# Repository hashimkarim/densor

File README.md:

# Densor

## About the project

Densor is an intraoral sensor platform, attached to regular dental retainers or aligners, that can take measurements inside the mouth. 

## Rationale

At present, in mouth measurements are typically made with external tools and in a controlled labaratory setting. Thus, real data from users daily lives is missing. To overcome this, we propose using widely used deltal retainers (or aligners), and enhance them with the Densor sensing platform. This way data is collected from inside the mouth without external tools. 

## Features

1. **Contactless transmission:** Densor is completely sealed and interacts with a smartphone via [NFC protocol](https://en.wikipedia.org/wiki/Near-field_communication). 
2. **Energy harvesting:** To stay powered Densor harvests energy, either from the [NFC communication itself](https://github.com/TUDSSL/densor/tree/master/NFC_harvester_battery_free) or from the [temperature gradient between the body and cold water](https://github.com/TUDSSL/densor/tree/master/TEG_harvester_battery_free). 
4. **Free of external hardware:** Operating Densor does not require any specialized tools, other than a NFC-compatible smartphone.

## Project layout

For the current NFC firmware (R2/R3 multirate logging), Android app, build
commands and protocol documentation, see the [software guide](NFC_harvester_battery_free/software/README.md).

This repository contains the design (both hardware and software) of two versions of Densor, based on the source of energy harvesting. Each version of the project is contained in its own folder:

1. **[Densor with NFC-based energy harvesting from a smartphone](https://github.com/TUDSSL/densor/tree/master/NFC_harvester_battery_free)**, as presented in [this research article](https://dl.acm.org/doi/10.1145/3699746);
2. **[Densor with thermoelectric energy harvesting from drinking cold water](https://github.com/TUDSSL/densor/tree/master/TEG_harvester_battery_free)**.

## Copyright

Copyright (C) 2024 TU Delft Embedded Systems Group/[Sustainable Systems Laboratory](https://github.com/TUDSSL).

MIT License or otherwise specified. See [license](https://github.com/TUDSSL/densor/blob/master/LICENSE.txt) file for details.

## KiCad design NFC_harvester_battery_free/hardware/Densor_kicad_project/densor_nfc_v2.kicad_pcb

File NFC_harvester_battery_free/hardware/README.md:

# Densor - Hardware

The TMP119 and its 100 nF capacitor sit **14.5 mm beyond the original PCB edge**.
R2/R3 remain **100 kΩ**, C14 connects `V_MCU` to `PSW`, and ALERT is unconnected.
The neck enforces 0.15 mm tracks for `V_MCU`/SDA/SCL and 0.20 mm for `PSW`,
with no vias/components; the continuous back GND fill and repaired GND connection remain.

[Current schematic](gerbers_schematic/schematic_nfc_baterry_free_fpc.pdf) ·
[Gerbers and drills](gerbers_schematic/gerbers_fpc) ·
[PCB layout](exports/pcb.pdf) · [3D render](exports/3d-oblique.png) ·
[BOM](exports/bom.csv) · [Placements](exports/placement.csv)

The original CAD stackup is retained, including its recorded **1.6 mm** thickness.
`exports/densor_nfc_v2.step` contains the native stackup and components;
`exports/board-1.6mm.step` is the nominal board envelope. Actual flex construction
and bend radius are unspecified in the original. Model sources and licenses are in
`Densor_kicad_project/vendor/`.

Latest checks: zero unrouted connections and no new DRC/ERC/parity findings.
The 31 DRC, 19 ERC and 20 metadata findings are inherited. Final I²C, wake/sleep
and bent/epoxied fit measurements across 2.6–1.8 V remain pending.
The purchasing links below are historical; use the schematic BOM for current
values, and complete its missing MPN fields before ordering.

## About the project 

This repository contains the design of Densor: an intraoral, actively powered, battery-free platform featuring multi-modal sensors and an extended lifespan. The repository consists of all components that make Densor:
- [Hardware](https://github.com/TUDSSL/densor/tree/master/NFC_harvester_battery_free/hardware)
- [Densor Firmware](https://github.com/TUDSSL/densor/tree/master/NFC_harvester_battery_free/software/DentalSensor_StorageProject)
- [Android app](https://github.com/TUDSSL/densor/tree/master/NFC_harvester_battery_free/software/source_ST25NFCApplication_V3_9)
- [Experiment setup and data collected](https://github.com/TUDSSL/densor/tree/master/NFC_harvester_battery_free/data/experiments)

This folder contains all the harware design files.

## Folder layout

- [KiCad project](Densor_kicad_project/densor_nfc_v2.kicad_pro): current design, local symbols, footprints and all 25 component STEP models.
- [Datasheets](datasheets): component reference PDFs.
- [Gerbers and schematic](gerbers_schematic): current extension Gerbers, drills, job file and schematic PDF.
- [Exports](exports): PCB views, renders, assembly drawings, BOM, placements and STEP files.

## Historical baseline purchasing references

| Component                  | Qty | Purchased from                                                                                                                                                                                                            |
|----------------------------|-----|---------------------------------------------------------------------------------------------------------------------------------------------------------------------------------------------------------------------------|
| Storage Capacitor          | 2   | [link to buy](https://www.digikey.com/en/products/detail/seiko-instruments/CPH3225A/8692444)                                                                                                                              |
| Decoupling Capacitor 100nF | 6   | [link to buy](https://nl.farnell.com/en-NL/kemet/c0603x104m4ractu/cap-mlcc-0-1uf-16v-0603/dp/2904941?st=0603%200.1uf)                                                                                                     |
| Zener Diode                | 1   | [link to buy](https://nl.farnell.com/on-semiconductor/mm3z3v6c/zener-diode-0-2w-3-6v-sod-323f/dp/2824925?CMP=i-ddd7-00001003)                                                                                             |
| Schottky Diode             | 1   | [link to buy](https://nl.farnell.com/nexperia/1ps76sb40-115/diode-schottky-sod323/dp/1349646?CMP=i-ddd7-00001003)                                                                                                         |
| Photo Diode                | 1   | [link to buy](https://nl.mouser.com/ProductDetail/Vishay-Semiconductors/VEMD1060X01?qs=pdQl6rENvLQkGyXPnNHd%2FQ%3D%3D&gclid=Cj0KCQjwmvSoBhDOARIsAK6aV7gSam9QYNxRe1G3dFcvfZGu4WvhXWOQdtZbTP3WNCzxGxyePn8TLa0aAiUbEALw_wcB) |
| Debug header               | 1   | [link to buy](https://nl.farnell.com/samtec/ftsh-105-01-l-d-k/connector-header-10pos-2row-1/dp/2856435?CMP=i-ddd7-00001003)                                                                                               |
| FPC connector              | 1   | [link to buy](https://nl.mouser.com/ProductDetail/Molex/503480-0800?qs=bodV9ulq6Gz33SKuZL445g%3D%3D&srsltid=AfmBOoqTYanmI1YXInVOzdpLIJ4tpVXYK3TQdvr3HJ4Y6jSj3ONDx022)                                                     |
| Pin Header 01x04           | 1   | [link to buy](https://nl.mouser.com/ProductDetail/Harwin/M20-9770446?qs=ulE8k0yEMYbCPpMPHeYh4w%3D%3D)                                                                                                                     |
| Resistor 100kohm           | 3   | [link to buy](https://nl.farnell.com/vishay/crcw0603100kfkea/res-100k-1-0-1w-0603-thick-film/dp/1469649?st=0603%20100k)                                                                                                   |
| Resistor 8Mohm             | 1   | [link to buy](https://nl.farnell.com/vishay/crcw06038m06fkea/res-8m06-1-0-1w-0603-thick-film/dp/2138717)                                                                                                                  |
| NFC Tag - ST25DV04K-JFR6D3 | 1   | [link to buy](https://www.digikey.nl/en/products/detail/stmicroelectronics/ST25DV64K-JFR6D3/7312974)                                                                                                                      |
| RTC - AM1805               | 1   | [link to buy](https://nl.farnell.com/en-NL/abracon/ab1805-t3/real-time-clock-i2c-qfn-16/dp/2467703?st=ab1805)                                                                                                             |
| MCU - STM32L021F3Ux        | 1   | [link to buy](https://www.digikey.nl/en/products/detail/stmicroelectronics/STM32L021F4U6TR/6166967)                                                                                                                       |
| Accelerometer - LIS2DW12   | 1   | [link to buy](https://nl.farnell.com/en-NL/stmicroelectronics/lis2dw12tr/lga-12-i-mems-digital-o-p-motion/dp/2849615?st=LIS2DW12TR)                                                                                       |
| SPDT - TS3A44159           | 1   | [link to buy](https://www.digikey.nl/en/products/detail/texas-instruments/TS3A44159RSVR/1909585)                                                                                                                          |
| Crystal                    | 1   | [link to buy](https://nl.farnell.com/en-NL/abracon/abs05w-32-768khz-j-2-t/crystal-32-768khz-4pf-smd-1-6/dp/2850126?st=abs05w)                                                                                             |
| Solder paste               | -   | [link to buy](https://www.digikey.nl/en/products/detail/chip-quik-inc/SMD291SNL50T3/5130160)                                                                                                                              |

## Copyright

Copyright (C) 2024 TU Delft Embedded Systems Group/Sustainable Systems Laboratory.

MIT Licence or otherwise specified. See [license](https://github.com/TUDSSL/ENGAGE/blob/master/LICENSE) file for details.

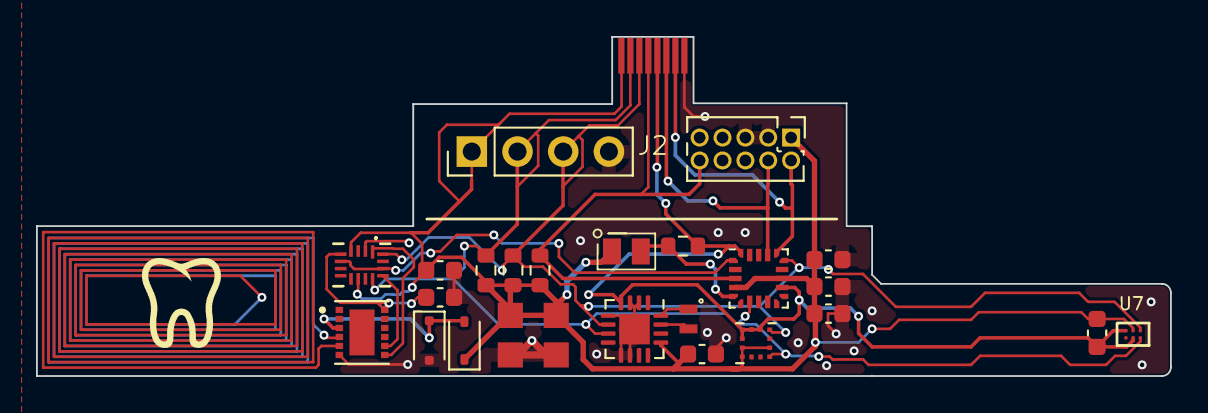
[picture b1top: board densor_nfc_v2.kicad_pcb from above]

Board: 2 copper layers, 63.0 x 18.8 mm, 26 parts (0 on the bottom side), 17 nets.

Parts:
C1, C2: C_Polarized; CPX3225A
C4, C5, C6, C7, C12, C13, C14: 100n; C_0603_1608Metric
D1: D_Zener_3v3; D_SOD-323F
D2: BAS316; D_SOD-323
D3: D_Photo; pd_vemd1060x01
J1: Conn_ARM_JTAG_SWD_10; PinHeader_2x05_P1.27mm_Vertical
J2: Conn_01x08_Pin; fpc_503480-0800
J3: Conn_01x04_Pin; PinHeader_1x04_P2.54mm_Vertical
R2, R3, R4: 100k; R_0603_1608Metric
R7: R; R_0603_1608Metric
U1: ST25DV04K-JFR6D3; PSON50P300X300X60-13N
U2: AM1805; QFN-16-1EP_3x3mm_P0.5mm_EP1.7x1.7mm
U4: STM32L011F3Ux; ST_UFQFPN-20_3x3mm_P0.5mm
U5: LIS2DW12; Kionix_LGA-12_2x2mm_P0.5mm_LayoutBorder2x4y
U6: TS3A44159; RSV16
U7: TMP119; DSBGA6_YBG_TEX
Y1: Crystal; ABS05W_Crystal

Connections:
/AC0: U1.4 (AC0), U1.5 (AC1)
/NFC_SWITCH: U4.1 (PC14), U6.6 (IN3-4), U6.14 (IN1-2)
/PSW: C14.2, J2.5, R7.2, U2.4 (PSW/nIRQ2), U4.12 (VSS), U4.20 (PB9), U5.5 (NC), U5.6 (GND), U5.7 (RES), U5.8 (GND), U7.B2, U7.C1
/V_EH: D1.1 (K), D2.2 (A), U1.3 (V_EH)
/V_MCU: C1.1, C2.1, C4.1, C5.2, C6.1, C7.2, C12.2, C14.1, D2.1 (K), D3.1 (K), J1.1 (VTref), J2.1, J3.1, R2.1, R3.1, R4.1, U2.13 (VCC), U4.4 (VDDA), U4.13 (VDD), U5.2 (CS), U5.9 (VDD), U5.10 (VDD_IO), U6.4 (COM3), U6.10 (VCC), U7.B1
/V_NFC_switched: C13.2, U1.12 (VCC), U6.5 (NC3)
/i2c_scl: J2.2, J3.2, R2.2, U2.7 (SCL), U4.7 (PA4), U5.1 (SCL), U6.12 (COM1), U7.A2
/i2c_scl_switched: U1.8 (SCL), U6.13 (NC1)
/i2c_sda: J2.3, J3.3, R3.2, U2.6 (SDA), U4.15 (PA10), U5.4 (SDA), U6.16 (COM2), U7.A1
/i2c_sda_switched: U1.7 (SDA), U6.1 (NC2)
/nRST_MCU: J1.10 (~RESET), J2.4, R4.2, U4.3 (NRST)
/pd: D3.2 (A), R7.1, U4.5 (PA0)
/swclk: J1.4 (SWDCLK/TCK), J2.6, U4.17 (PA14)
/swdio: J1.2 (SWDIO/TMS), J2.7, U4.16 (PA13)
GND: C1.2, C2.2, C4.2, C5.1, C6.2, C7.1, C12.1, C13.1, D1.2 (A), J1.3 (GND), J1.5 (GND), J2.8, J3.4, U1.6 (VSS), U2.2 (WDI), U2.3 (nEXTR), U2.5 (VBAT), U2.9 (VSS), U2.10 (EXTI), U2.17 (VSS), U6.2 (GND)
unnamed: U2.16 (XI), Y1.1
unnamed: U2.15 (XO), Y1.2

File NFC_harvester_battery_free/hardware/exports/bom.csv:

"References","Value","Footprint","Quantity","MPN","Manufacturer","DNP"
"C1,C2","C_Polarized","antennas:CPX3225A","2","","",""
"C4-C7,C12,C13","100n","Capacitor_SMD:C_0603_1608Metric","6","","",""
"C14","100n","Densor:C_0603_1608Metric","1","","",""
"D1","D_Zener_3v3","Diode_SMD:D_SOD-323F","1","","",""
"D2","BAS316","Diode_SMD:D_SOD-323","1","","",""
"D3","D_Photo","antennas:pd_vemd1060x01","1","","",""
"J1","Conn_ARM_JTAG_SWD_10","Connector_PinHeader_1.27mm:PinHeader_2x05_P1.27mm_Vertical","1","","",""
"J2","Conn_01x08_Pin","antennas:fpc_503480-0800","1","","",""
"J3","Conn_01x04_Pin","Connector_PinHeader_2.54mm:PinHeader_1x04_P2.54mm_Vertical","1","","",""
"R2-R4","100k","Resistor_SMD:R_0603_1608Metric","3","","",""
"R7","R","Resistor_SMD:R_0603_1608Metric","1","","",""
"U1","ST25DV04K-JFR6D3","ST25DV04K-JFR6D3:PSON50P300X300X60-13N","1","","",""
"U2","AM1805","Package_DFN_QFN:QFN-16-1EP_3x3mm_P0.5mm_EP1.7x1.7mm","1","","",""
"U4","STM32L011F3Ux","Package_DFN_QFN:ST_UFQFPN-20_3x3mm_P0.5mm","1","","",""
"U5","LIS2DW12","Package_LGA:Kionix_LGA-12_2x2mm_P0.5mm_LayoutBorder2x4y","1","","",""
"U6","TS3A44159","antennas:RSV16","1","","",""
"U7","TMP119","Densor:DSBGA6_YBG_TEX","1","TMP119AIYBGR","Texas Instruments",""
"Y1","Crystal","antennas:ABS05W_Crystal","1","","",""
